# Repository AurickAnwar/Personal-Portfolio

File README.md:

# Personal Portfolio Website

A modern, responsive personal portfolio website built with React.js featuring a clean design and smooth animations.

## Features

- **Responsive Design**: Works perfectly on desktop, tablet, and mobile devices
- **Modern UI**: Clean, professional design with gradient accents and smooth animations
- **Navigation**: Simple navigation with Home, Projects, and Contact sections
- **Interactive Elements**: Hover effects, smooth scrolling, and animated components
- **Contact Form**: Functional contact form with validation
- **Project Showcase**: Grid layout displaying projects with technology tags

## Sections

### Home
- Personal introduction and title
- Professional description
- Call-to-action buttons
- Statistics section
- Animated profile placeholder

### Projects
- Grid layout showcasing 6 sample projects
- Project cards with images, descriptions, and technology tags
- Live demo and GitHub links
- Hover effects and smooth animations

### Contact
- Contact information with icons
- Functional contact form
- Form validation and submission feedback
- Social media links

## Technologies Used

- React 18
- React Router DOM
- CSS3 with modern features
- Responsive Grid and Flexbox
- CSS Animations and Transitions

## Getting Started

### Prerequisites

- Node.js (version 14 or higher)
- npm or yarn package manager

### Installation

1. Navigate to the project directory:
   ```bash
   cd personal-portfolio
   ```

2. Install dependencies:
   ```bash
   npm install
   ```

3. Start the development server:
   ```bash
   npm start
   ```

4. Open your browser and visit `http://localhost:3000`

### Building for Production

To create a production build:

```bash
npm run build
```

The build files will be in the `build` directory.

## Customization

### Personal Information
Update the following files with your personal information:

- `src/components/Home.js` - Update name, title, and description
- `src/components/Contact.js` - Update contact information
- `src/components/Projects.js` - Replace sample projects with your own

### Styling
- Modify `src/index.css` for global styles
- Update component-specific CSS files for individual styling
- Change color scheme by updating CSS custom properties

### Adding Projects
Edit `src/components/Projects.js` to add your own projects:

```javascript
const projects = [
  {
    id: 1,
    title: "Your Project Title",
    description: "Project description...",
    image: "path/to/image.jpg",
    technologies: ["React", "Node.js", "MongoDB"],
    liveUrl: "https://your-project.com",
    githubUrl: "https://github.com/yourusername/project"
  },
  // Add more projects...
];
```

## Deployment

This project can be deployed to various platforms:

- **Netlify**: Connect your GitHub repository for automatic deployments
- **Vercel**: Deploy with zero configuration
- **GitHub Pages**: Use the `gh-pages` package for deployment

## Browser Support

- Chrome (latest)
- Firefox (latest)
- Safari (latest)
- Edge (latest)

## License

This project is open source and available under the [MIT License](LICENSE).

## Contributing

Feel free to submit issues and enhancement requests!

---

**Note**: Remember to replace placeholder content with your actual information before deploying.

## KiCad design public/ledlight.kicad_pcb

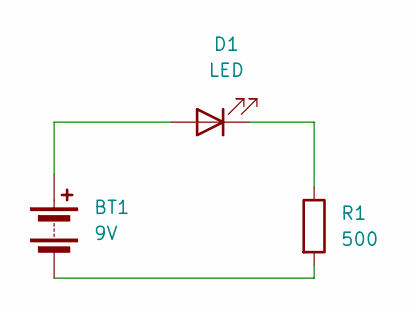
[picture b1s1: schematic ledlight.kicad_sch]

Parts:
BT1: 9V; PinHeader_1x02_P2.54mm_Vertical
D1: LED; LED_D5.0mm
R1: 500; R_Axial_DIN0207_L6.3mm_D2.5mm_P7.62mm_Horizontal

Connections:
unnamed: BT1.1 (+), D1.2 (A)
unnamed: BT1.2 (-), R1.2
unnamed: D1.1 (K), R1.1

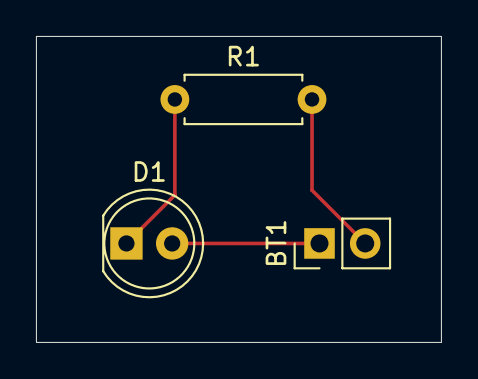
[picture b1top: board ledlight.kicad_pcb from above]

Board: 2 copper layers, 22.5 x 17.0 mm, 3 parts (0 on the bottom side), 3 nets.

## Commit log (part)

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2025-09-18 Fix package.json syntax for Vercel
2025-09-18 Clean dependencies for Vercel
2025-09-18 Fix .gitignore filename
2025-09-18 Reinstall dependencies
2025-09-18 Fix Vercel deployment configuration
2025-09-18 Fix image paths for Vercel deployment
2025-09-18 Implement robust image path solution using process.env.PUBLIC_URL for Vercel compatibility
2025-09-18 Add centralized image utility and improve asset path handling
2025-09-18 Fix Vercel routing for static files and simplify image paths
2025-09-18 Fix Mobile caching issue
2025-11-20 Update site
2025-11-20 Serve IAM files on Vercel
2025-11-22 Update 3D Modelled Drone project: change STL File to Assembly File
2025-11-23 Add Audi S2 Steering Wheel image and STL file
2026-02-16 Update portfolio
2026-03-06 Refactor: blue AI accent palette (navbar, projects, home, contact, hero)
    Made-with: Cursor
2026-03-30 Update Github
2026-04-22 Update Website
2026-04-22 Update Changes
2026-06-01 Added updated Facial Recognition Project
2026-06-03 Updated ROS Learning
2026-06-04 made auto load if user types yes to make it easier with people with phone
2026-06-04 Fixed Transition
2026-06-04 Moved UFC prediction above Basketball
2026-06-04 Added description and progression to ROS2
2026-06-04 Didn't get into Mechatronics
2026-06-04 Updated Resume to Engineering Physics
2026-06-04 Update Resume
2026-06-06 Change Date for Knicks vs Spurs
2026-06-07 Change ROS2 Learning
2026-06-07 Added Bracket
2026-06-09 Knicks vs Spurs Game 3
2026-06-09 Fixed Resume
2026-06-09 Added Work experience to fron home page
2026-06-09 Added Logo
2026-06-09 Added some more images
2026-06-09 Added extra lighting to button
2026-06-09 Added Cursor different mouse
2026-06-11 Added Knicks vs Spurs game 5
2026-06-11 Added Resume
2026-06-11 Added hyperlinks to resume
2026-06-11 Update loading page
2026-06-12 Trying to make it compatible on Iphone
2026-06-12 Made changes just for Iphone
2026-06-12 Added robot head
2026-06-12 Fixed image takeover path
2026-06-12 Added activate killshot on Iphone
2026-06-13 Made an evolution style intro
2026-06-13 Breast Cancer Cell Detection
2026-06-13 Added some more photos
2026-06-13 Cropped Image
2026-06-13 Update Image
2026-06-14 2ND INTERNSHIP BABY
2026-06-14 Knicks are NBA Champions
2026-06-14 Update Knicks vs Spurs
2026-06-14 Made intro loader shorter
2026-06-14 Added a portfolio just for recruiters
2026-06-15 Changed Title for recruitment
2026-06-15 Changed up style
2026-06-15 Update fight results
2026-06-15 Updated Fights
2026-06-15 Update Holloway vs Mcgregor
2026-06-16 Fixed up work experience
2026-06-16 Made more user friendly
2026-06-17 Fixed scrol
2026-06-17 Added all Changes
2026-06-18 Updated Progress for Breast Cancer
2026-06-18 Added currently building to recruitment
2026-06-18 Removed currently building
2026-06-18 Update Project
2026-06-18 Fixed recruitment page
2026-06-22 Update Navbar
2026-06-26 Updated ROS2
2026-06-27 Update ROS2 Progress
2026-06-28 World Cup 2026 Predictions
2026-06-29 Update Bracket
2026-06-30 Update Locations for Life Photos
